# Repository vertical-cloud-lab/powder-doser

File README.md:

# Powder doser

**An open-source powder doser for autonomous alloy discovery, designed by engineers and modelled by AI agents.**

<p align="center">
  <a href="https://vertical-cloud-lab.github.io/powder-doser/"><b>Project page</b></a> ·
  <a href="https://github.com/vertical-cloud-lab/powder-doser/pull/209">Paper (in prep.)</a> ·
  <a href="https://vertical-cloud-lab.github.io/powder-doser/#build">CAD</a> ·
  <a href="https://www.youtube.com/watch?v=YmvaeqOQAU4&amp;t=514s">Talk</a> ·
  <a href="https://vertical-cloud-lab.github.io/powder-doser/#videos">Videos</a> ·
  <a href="https://vertical-cloud-lab.github.io/powder-doser/static/powder-doser-poster.pdf">Poster</a> ·
  <a href="https://vertical-cloud-lab.github.io/powder-doser/#talks">TMS 2027</a>
</p>

We built this doser at BYU's [Vertical Cloud Lab](https://github.com/vertical-cloud-lab) from 3D-printed parts and off-the-shelf electronics, for under $200 plus an analytical balance. One printed tube is both the powder reservoir and the dosing screw: the doser turns, tilts and taps it over a cup on the balance, which closes the loop, and an AI agent runs a dose when someone asks for one in a GitHub comment. Every 1 g dose on seven of the 13 powders we tested landed within ±5% of the target. **The [project page](https://vertical-cloud-lab.github.io/powder-doser/) has the rest:** the paper's figures, the CAD and firmware, the talk and videos, the poster and the TMS 2027 abstracts. The design discussion, the AI agents' work and the run data are in this repository's issues and pull requests.

<p align="center"></p>

<sub><b>Claude doses 8 g of Al 4047 for an atomizer charge</b> (30 Sep 2026, [#166](https://github.com/vertical-cloud-lab/powder-doser/pull/166)). Left, a phone's screen recording of the pull-request thread: Claude's checklist while the first pass runs, the follow-up to <code>@claude</code> typed on the phone after a clog, Claude's plan for a top-up, and its report. Right, the fixed camera over the balance at the same moment. 59 minutes in 22 s, sped up as marked. The full teaser on the [project page](https://vertical-cloud-lab.github.io/powder-doser/) starts with the auger being fitted.</sub>

<p align="center"></p>

<sub><b>A dose in three phases, replayed on the CAD</b> with the mass logged in the cup: bulk at 40° and 100 rpm with taps until 300 mg is left, trickle at 10° with no taps, then single taps at 15° until within 3 mg. The values in blue are the ones the optimizer sets, here the settings it recommended for 0.5 g of salt in the optimization campaign ([#166](https://github.com/vertical-cloud-lab/powder-doser/pull/166)), not those of the tests in the paper. Sped up as marked; from the campaign's slides ([#175](https://github.com/vertical-cloud-lab/powder-doser/pull/175)).</sub>

## Citation

Until the paper is out, please cite the repository:

```bibtex
@misc{charles2026powderdoser,
  title        = {An open-source powder doser for autonomous alloy discovery,
                  designed by engineers and modelled by AI agents},
  author       = {Charles, Sam and Mulberry, Will and Winters, Luke and
                  Robison, Carl and Erickson, Gage and Baird, Sterling G.},
  year         = {2026},
  note         = {Manuscript in preparation},
  howpublished = {\url{https://github.com/vertical-cloud-lab/powder-doser}}
}
```

## Outreach

A running list of individuals, academic groups, commercial vendors, and
open-source projects we could reach out to for help with accurate, automated
powder dispensing is kept in
[`paper/background/07-powder-dispensing-outreach-contacts.md`](paper/background/07-powder-dispensing-outreach-contacts.md)
(Edison-backed; per-entry `### Name` anchors and verifiable `(source: <URL>)`
tags). The synthesis is produced by
[`paper/background/edison_run_powder_dispensing_outreach_contacts.py`](paper/background/edison_run_powder_dispensing_outreach_contacts.py),
with raw artifacts under
[`paper/background/edison_artifacts/`](paper/background/edison_artifacts/),
and is compiled from the accelerated-discovery forum thread on [accurate
powder dispensing for chemistry and
materials-science applications](https://accelerated-discovery.org/t/accurate-powder-dispensing-for-chemistry-and-materials-science-applications/177),
the background notes in
[#29](https://github.com/vertical-cloud-lab/powder-doser/pull/29), and other
references throughout this repository. Same workflow as the generative-CAD
outreach note in [#43](https://github.com/vertical-cloud-lab/powder-doser/pull/43).

A companion list of **powder-properties** experts (flowability and
cohesion/friction measurement, DEM modeling and Bayesian calibration, AM
spreadability and powder-bed metrology) — anchored to the TMS 2027
calibration-optimization abstract from
[#78](https://github.com/vertical-cloud-lab/powder-doser/pull/78) — is kept
in
[`paper/background/08-powder-properties-experts.md`](paper/background/08-powder-properties-experts.md),
produced by
[`paper/background/edison_run_powder_properties_experts.py`](paper/background/edison_run_powder_properties_experts.py)
(three Edison `LITERATURE_HIGH` tasks plus direct web searching; raw
artifacts under the same
[`paper/background/edison_artifacts/`](paper/background/edison_artifacts/)
directory).

For actually reaching out, a narrowed **12-person shortlist** of the
powder-properties contacts who can *truly* help characterize powder for the
dynamic (DEM / cohesive-frictional) models — anchored to the on-device
characterization sweeps and tap / rapid-dose tests in
[#131](https://github.com/vertical-cloud-lab/powder-doser/pull/131), each with
a ready-to-send **template email** — is kept in
[`paper/background/09-powder-characterization-outreach-emails.md`](paper/background/09-powder-characterization-outreach-emails.md).

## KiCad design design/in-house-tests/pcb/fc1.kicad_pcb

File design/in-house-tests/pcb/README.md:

# FC-1: Faraday-cup charge amplifier board

**Status: design v1.0, 2026-11-28. Not built or tested.** KiCad 9.0.8 project for test 10 of
[`../SPEC.md`](../SPEC.md) (Faraday cup). ERC: 0 errors, 0 warnings. DRC: 0 errors, 0 unconnected pads,
schematic parity clean; 55 warnings, all the deliberate solder-mask opening over the guard (see
[Checks](#checks)).

| Top | Bottom (mirrored) |
|---|---|
|  |  |

Schematic: [`fc1-schematic.pdf`](fc1-schematic.pdf) ([SVG](fc1-schematic.svg), [PNG](fc1-schematic.png)).

## What it does

The inner cup of the Faraday cup is wired to the BNC. The board holds the cup at a virtual ground
and moves every coulomb that lands in the cup onto a feedback capacitor C_f. The output voltage is
proportional to the charge:

    Q_cup = -C_f * (V_OUT - V_REF)

An ADS1115 on the board reads V_OUT - V_REF differentially. It sits on the accessory Pico 2 W's
I2C chain (STEMMA QT, 3.3 V) at address 0x48. A reed relay across C_f zeroes the integrator when
the Pico drives GP10 high.

## The circuit in words

- **Input (guarded).** BNC J1 (Amphenol RF 031-5539, polypropylene insulator) centre pin to the
  inverting input of U1 (ADA4530-1, femtoampere electrometer op-amp, SOIC-8). This node, SUM, also
  goes to one side of C1, C2, R1 and the reed contact K1 pin 1, and nothing else. It is routed on the
  top layer only, with no vias. The only plated holes on it are the BNC centre pin and K1 pin 1.
- **Guard.** U1's guard-buffer pins (2 and 7) drive a GUARD copper fill around every SUM pad and
  trace, on both layers, 0.5 mm from SUM. The relay's coaxial shield (K1 pin 5) is on GUARD, so leakage
  from the coil lands on the guard, not on SUM. There is no solder mask over the guarded area (top and
  bottom), so surface leakage from other copper is caught by bare guard copper. A 2.2 mm hole (H6)
  next to U1 takes a Keystone 11301 PTFE turret if you want to air-wire the input instead.
- **Integrator.** C1 = 10 nF C0G 1 % is always in the feedback. Fitting the shunt on JP1 adds
  C2 = 100 nF C0G in parallel (C_f = 110 nF). R1 (1206, not fitted) is a place for a 10 G bleed
  resistor if slow drift ever matters more than holding a reading.
- **Reference.** U2 (REF3025, 2.500 V) sets U1's non-inverting input, the virtual ground, to mid-rail.
- **Reset.** K1 (Coto 9002-05-01: 1 Form A reed, 10^12 ohm minimum insulation, coaxial shield,
  internal coil diode) shorts C_f through R2 (100 R, limits the discharge current through the reed).
  GP10 high -> R11 4k7 -> Q1 (MMBT3904) pulls the 350 ohm, 5 V coil low (14 mA). D1 (1N4148W) is the
  flyback diode; R12 holds Q1 off if RESET_IN floats. D2 (yellow) lights while the relay is closed.
- **ADC.** U3 (ADS1115) runs at 5 V so it can see the whole 0-5 V output swing. AIN0 = OUT through
  R3 1k / C7 10 nF C0G, AIN1 = REF through the matching R4 / C8. AIN2, AIN3 and ALERT are unused.
  Address 0x48 through R10 (100k to GND); bridge one of JP2 / JP3 / JP4 for 0x49 / 0x4A / 0x4B.
- **I2C.** Q2, Q3 (BSS138) shift SDA and SCL between the 3.3 V bus (pull-ups R6, R7) and the ADC's
  5 V side (R8, R9). J2 and J3 are STEMMA QT / Qwiic sockets in parallel (pass-through).
- **Power.** 5 V from the Pico's VBUS on J4 pin 2. R5 (10 R) and C4 (10 uF) filter it into +5VA for
  U1, U2, U3. No LDO: U1's supply rejection and the differential read (REF noise cancels) make one
  unnecessary, and an LDO would leave too little headroom from 5 V (U1 needs at least 4.5 V). The
  relay coil and LEDs run on the unfiltered +5V. 3.3 V comes from the Pico (J4 pin 3 or the QT cable).
  D3 (green) shows 5 V.
- **Grounds.** One GND net poured on both layers and joined by 59 vias; no split planes (all
  currents are DC and under 20 mA). The outer can's M3 lug H5 joins GND only through R15 (0 R) near
  J4's GND pin: that is the single point where the shield meets circuit ground. Remove R15 to float the
  can, or replace it with an RC. JP5 sets the BNC shell: pads 1-2 bridged = shell on GND (default);
  2-3 = shell on GUARD (see [Leakage](#leakage-and-drift)).
- **Header J4** (2.54 mm): 1 GND, 2 5V, 3 3V3, 4 SDA, 5 SCL, 6 RESET_IN.

## Design numbers

### Range and resolution

U1's output swings to within about 0.1 V of the rails, so V_OUT - V_REF spans about +/-2.4 V.

| | C_f = 10 nF (JP1 open) | C_f = 110 nF (JP1 fitted) |
|---|---|---|
| Full scale | about +/-24 nC | about +/-264 nC |
| ADS1115 +/-4.096 V range (LSB 125 uV) | 1.25 pC per LSB | 13.8 pC per LSB |
| +/-2.048 V range (62.5 uV) | 0.63 pC | 6.9 pC |
| +/-0.256 V range (7.8 uV), for under 2.5 nC / 28 nC | 0.078 pC | 0.86 pC |

SPEC §10 expects 1-100 nC per gram, so a 0.1-1 g dose gives 0.1-100 nC: the 10 nF range for most
doses, 110 nF above about 20 nC. Auto-range in firmware by stepping the ADS1115's gain.

### Leakage and drift

A constant input current I moves the output by I * t / C_f.

| Source | Size | Drift on 10 nF | on 110 nF |
|---|---|---|---|
| U1 input bias (20 fA maximum: SPEC §10 and ADI's headline figure, not re-read here) | 20 fA | 1.2 pC/min = 0.12 mV/min | 0.011 mV/min |
| Reed contacts, open, 10^12 ohm minimum (10^13 typical) | proportional to the reading: 2.4 pA at full scale | at most 0.6 % of the reading per minute | same in % |
| Coil to contact | goes to the guarded shield, not to SUM | negligible | negligible |
| BNC and cable insulation, shell on GND (JP5 1-2) | 2.5 V across them; tens of fA when clean | about 0.1-1 pC/min | |
| FR-4 gap between the BNC centre and shell pins (0.94 mm, unguarded when JP5 is 1-2) | sub-pA clean and dry, can reach pA when humid or dirty | up to tens of pC/min | |

The last row is the weak point of a vertical BNC: its shell pin sits 2.54 mm from the centre pin, too
close for a guard trace. For charges under about 1 nC, or above about 50 % RH, bridge JP5 2-3 instead:
the shell (and the cable shield) then sit at the guard voltage, so there is no voltage across the BNC,
the cable or that gap. In that mode the cable shield must not touch the grounded outer can (use an
insulated feed-through at the can, ground the can with the lug H5), and the BNC must not touch a
grounded metal panel. The leakage figures for the gap are estimates, not measurements: measure the
drift with the drift test below and log RH with the SHT45.

The relay term acts like a 10^12 ohm resistor across C_f (time constant 10^4 s on 10 nF), so a reading
taken within a minute of the reset loses at most about 0.6 % and usually much less.

### Reset

- K1 closes in about 0.35 ms (Coto data sheet, typical, including bounce).
- C_f discharges through R2: time constant 1 us (10 nF) or 11 us (110 nF); U1 then holds OUT = REF.
- Recommended: GP10 high for 100 ms (1 s after a near-full-scale reading), then low, wait 50 ms, take
  the baseline reading.
- Opening the relay injects a small fixed charge (the coil swings 5 V; coil-to-contact capacitance
  is 0.5 pF with the shield guarded, so at most about 2.5 pC). The baseline taken after release
  removes it.

### Dielectric absorption

After a reset, a capacitor gives back a small fraction of its previous voltage over seconds to
minutes. C0G ceramic is among the best dielectrics for this (typically 0.1 % or less), with
polypropylene or polystyrene film better still. After a full-scale 2.4 V reading, expect at most a
few mV (tens of pC on 10 nF) to creep back. Hold the reset for 1 s after large readings and always
read a fresh baseline after the reset. If it matters, replace C1 with a 10 nF polypropylene film
capacitor on short leads (WIMA FKP2) on the same pads.

### Input capacitance and noise gain

C_in = cup to can (10-30 pF) + cable (RG-58 is about 100 pF/m: about 30 pF for 0.3 m) + BNC, PCB and
U1 (a few pF): about 50-70 pF. The charge amplifier collects the charge regardless of C_in (the cup
stays at the virtual ground), but C_in sets the noise gain 1 + C_in / C_f = 1.006 on 10 nF and
1.0006 on 110 nF. So U1's voltage noise reaches the output almost unamplified: a few uV, far below
the ADC's LSB. Because the cup sits at +2.5 V relative to the grounded can, a change in their
capacitance moves charge: 0.1 pF of vibration or powder gives 0.25 pC. That sets a floor for the
smallest charges, not for nC readings.

## Board

- 50 x 40 mm, 2 layers, 1.6 mm FR-4, 1 oz. Four M3 holes (NPTH) 3.5 mm from each corner
  (43 x 33 mm pattern), M3 plated lug H5 for the outer can, 2.2 mm hole H6 for the PTFE turret.
- Hand-solderable: 0805 and 1206 passives, SOT-23, SOD-123, SOIC-8, MSOP-10 (0.5 mm pitch, the
  hardest part), JST SH sockets, through-hole headers, relay and BNC.
- Design rules (JLCPCB- and OSH Park-safe): 0.15 mm minimum track and clearance, 0.6 / 0.3 mm vias,
  0.3 mm copper to edge. Default clearance 0.2 mm, SUM 0.5 mm. `fc1.kicad_dru` allows the MSOP-10's
  own 0.15 mm pad gaps.
- Silkscreen: name, version, date, J4 pin names, LED and range labels, address codes, JP5 pads, CAN.
  `JLCJLCJLCJLC` on the back marks where JLCPCB may print its order number (keep it off the guard).

## Ordering

| Fab | Price | Build + shipping to Utah | Source |
|---|---|---|---|
| JLCPCB | from $2 for 5 boards (2 layers, up to 100 x 100 mm, green, HASL); ENIG extra | 24 h build (green); DHL Express 3-5 business days, Global Standard Direct Line 8-10 | jlcpcb.com home page offer; shipping table at jlcpcb.com/help/article/Shipping-Methods-and-Delivery-Time (updated 2026-11-10) |
| OSH Park | $5 per square inch for 3: 3.10 in^2 = **$15.50 for 3** (ENIG, purple, 1.6 mm) | ships in 9-12 calendar days, free USPS First Class 1-5 business days; Super Swift $31.00, ships within 5 business days | docs.oshpark.com (services/two-layer, super-swift, shipping-information) |

Not verified: the exact JLCPCB quote for this board and the shipping cost (both need the quote page
in a browser). Expect about 1 week door to door from JLCPCB with DHL, about 2-2.5 weeks from OSH Park.

- **JLCPCB:** upload `fc1-gerbers.zip`; 2 layers, 1.6 mm, 50 x 40 mm, qty 5. Pick **ENIG** if you
  can (the guard area is bare copper; HASL works but is lumpier). Order number: "Specify a location".
  Do not let anyone "fix" the mask opening over the input: it is on purpose.
- **OSH Park:** upload `fc1-gerbers.zip` (or `fc1.kicad_pcb`). ENIG is standard.
- **Parts:** [`bom.csv`](bom.csv): 29 part lines (40 parts fitted, R1 not fitted) plus the optional PTFE turret and the PCB, with DigiKey part numbers, prices and stock read from
  DigiKey's own product pages on 2026-11-28. About **$72 per board** at single-unit prices, about
  $58 at 10-off prices, plus the PCB. The ADA4530-1 alone is $41.95 (103 in stock, 44-week factory
  lead time: buy it first). Out-of-stock first choices were swapped for in-stock equivalents (listed
  as alternates). The JST, header and Ohmite alternates were not checked.

## Assembly

[`solder_steps.json`](solder_steps.json) lists the 41 steps in order (also the source for the
soldering animation): ICs first (U3, U1), then SOT-23 and SOD-123 parts, the 0805 resistors and
capacitors, LEDs, the 1206 parts, the JP5 bridge, the JST sockets, the headers, the relay and
finally the BNC. Positions are in mm from the board's lower-left corner, y up.

- Use rosin or water-washable flux, not no-clean, and wash the whole board in 99 % IPA with a soft
  brush. Rinse the guard area last with fresh IPA, then dry it (warm air or 1 h at 50 C).
- Hold the board by its edges after washing; skin oil on the guard area is a leakage path.
- Bridge JP5 pads 1-2 (shell on GND) for the first tests. Leave JP2-JP4 open (address 0x48).
- R1 is not fitted. Fit the JP1 shunt only for the 110 nF range.

## Bench test

1. **Power.** Wire J4 to the Pico: GND, 5V to VBUS (pin 40), 3V3 to 3V3(OUT) (pin 36), SDA to GP0,
   SCL to GP1, RST to GP10. Always connect J4's 5 V: with 3.3 V but no 5 V, the BSS138 body diodes
   load the I2C bus and the other sensors on the chain stop answering. Check: D3 on; REF at C6 =
   2.500 V +/- 5 mV; the bare guard copper reads the same about 2.50 V on a DMM (never probe SUM);
   an I2C scan shows 0x48; D2 lights while GP10 is high.
2. **Drift (leakage).** Cap the BNC, reset, log OUT - REF at 8 SPS on the +/-0.256 V range for 10 min.
   Leakage I = C_f * slope. Clean and dry, expect under 0.12 mV/min on 10 nF (20 fA). Log RH and T.
3. **Known charge.** Put a 1.00 nF +/-1 % C0G capacitor in series with the BNC centre (a BNC tee or a
   short BNC-to-clip lead), its other end on a source that steps from 0 to 1.000 V, with the source's
   ground on the board's GND. Q = C_inj * dV = 1.00 nC, so V_OUT - V_REF should step by
   **-100.0 mV** on 10 nF and **-9.09 mV** on 110 nF. Stepping back to 0 V should return it to the
   baseline. Other useful points: 10.0 nF injection -> -1.000 V on 10 nF (gain -1: checks C1 against
   C_inj); 10 pF -> 10 pC -> -1.00 mV (use the +/-0.256 V range). The Pico can be the source: a GPIO
   step is 3.3 V, so 1 nF injects 3.3 nC (measure the GPIO's high level with a DMM first).
4. **Reset.** Inject 10 nC, pulse GP10 for 100 ms: the reading should come back to the baseline
   within a few LSB. Log the next 60 s to see the dielectric-absorption creep.
5. **Range.** Fit JP1 and repeat step 3 with a 10.0 nF injection: expect -90.9 mV.

## Reading it from the accessory Pico

I2C0 on GP0 (SDA) / GP1 (SCL), address 0x48. ADS1115 config register (0x01) for a single-shot
AIN0 - AIN1 conversion at 8 SPS, comparator off: `0x8303` (+/-4.096 V, the full swing), `0x8503`
(+/-2.048 V), `0x8B03` (+/-0.256 V). Use 8 SPS for single readings (lowest noise) and 128-860 SPS
for time series. Reset is GP10 (SPEC §0.2): high = relay closed.

```python
# MicroPython, accessory Pico 2 W
from machine import I2C, Pin
import struct, time

i2c = I2C(0, sda=Pin(0), scl=Pin(1), freq=100_000)
rst = Pin(10, Pin.OUT, value=0)
ADDR, C_F = 0x48, 10e-9            # 110e-9 with the JP1 shunt fitted
PGA = {4.096: 1, 2.048: 2, 1.024: 3, 0.512: 4, 0.256: 5}

def volts(fsr=4.096):
    """One AIN0-AIN1 reading at 8 SPS, in volts (V_OUT - V_REF)."""
    cfg = 0x8000 | (PGA[fsr] << 9) | 0x0100 | 0x0003   # OS, AIN0-AIN1, gain, single-shot, 8 SPS, comp off
    i2c.writeto_mem(ADDR, 0x01, struct.pack(">H", cfg))
    while not i2c.readfrom_mem(ADDR, 0x01, 2)[0] & 0x80:
        time.sleep_ms(5)
    return struct.unpack(">h", i2c.readfrom_mem(ADDR, 0x00, 2))[0] * fsr / 32768

def zero(hold_ms=100):
    rst.on(); time.sleep_ms(hold_ms); rst.off(); time.sleep_ms(50)
    return volts()

v0 = zero()
# ... dose N revs, wait 2 s after the last grain (SPEC §10) ...
q = -C_F * (volts() - v0)          # coulombs collected by the inner cup
```

## Files

| File | What |
|---|---|
| `fc1.kicad_pro`, `fc1.kicad_sch`, `fc1.kicad_pcb`, `fc1.kicad_dru` | KiCad 9 project |
| `fc1.kicad_sym`, `fc1.pretty/`, `sym-lib-table`, `fp-lib-table` | project library: the Coto 9002 symbol and SIP-6 footprint (drawn from the Coto data sheet; everything else is from KiCad's own libraries) |
| `fc1_design.py` | single source: parts, nets, MPNs, placement, guard polygon, silkscreen |
| `gen_sch.py`, `gen_pro.py`, `build_pcb.py`, `sexp.py` | generators for the schematic, project file and board |
| `fc1.dsn`, `fc1.ses` | autorouter input and result (FreeRouting 2.6.0) |
| `make_bom.py`, `bom.csv` | BOM with DigiKey data |
| `make_solder_steps.py`, `solder_steps.json` | soldering order and geometry for the animation |
| `export.sh` | ERC, DRC, schematic PDF/SVG, Gerbers, drill, position file and renders |
| `fc1-schematic.pdf/.svg/.png`, `fc1-top.png`, `fc1-bottom.png`, `fc1-iso.png` | outputs |
| `gerbers/`, `fc1-gerbers.zip`, `fc1-pos.csv` | fabrication outputs (position file origin = board lower-left, y up) |
| `erc.rpt`, `drc.rpt` | check reports |

To regenerate (KiCad 9 `pcbnew` needs the system Python):

```bash
python3 gen_pro.py && python3 gen_sch.py
/usr/bin/python3 build_pcb.py place          # footprints, nets, the hand-routed guarded input
/usr/bin/python3 build_pcb.py dsn            # fc1.dsn with the guard area kept out
java -jar freerouting-2.6.0.jar -de fc1.dsn -do fc1.ses -mp 40 -mt 1 --gui.enabled=false   # Java 25
/usr/bin/python3 build_pcb.py finish         # import routes, guard and GND pours, mask opening, silk
./export.sh && python3 make_bom.py && /usr/bin/python3 make_solder_steps.py
```

The hand-routed parts are the SUM traces, the guard link between U1 pins 7 and 2, U1's feedback
connections and the BNC shell link; FreeRouting routed the rest (some traces neck to 0.15 mm at the
MSOP-10 pins). The renders used the 12 KiCad 3D models this board needs, fetched from
gitlab.com/kicad/libraries/kicad-packages3D (tag 9.0.8); KiCad has no model for the BNC and the relay
footprint is the project's own, so those two show as bare pads.

## Checks

- **ERC** ([`erc.rpt`](erc.rpt)): 0 errors, 0 warnings. A netlist export was also compared pin by pin
  with `fc1_design.py`: no differences.
- **DRC** ([`drc.rpt`](drc.rpt), with schematic parity): 0 errors, 0 unconnected pads, 0 footprint or
  parity problems. 55 warnings, all `solder_mask_bridge`: the mask opening over the guarded area
  exposes SUM and GUARD copper (and 14 GUARD vias) in one aperture. That is the intended guard layout,
  not a fault.

## Not verified / open points

- **ADA4530-1 pinout** is from KiCad's library symbol (1 +IN, 2 and 7 guard, 3 "IC", 4 V-, 5 V+,
  6 OUT, 8 -IN); analog.com timed out from the runner, so the data sheet was not re-read. Pin 3 is
  left unconnected. Check pin 3 and the guard-buffer load limits against the data sheet before ordering.
- **Coto 9002 footprint** was drawn from the data sheet (6 pins on a 2.54 mm grid: 1, 5, 2, gap, 3,
  6, 4; body 19.3 x 5.08 mm, 5.6 mm with shell). Check it against a real relay or a 1:1 print.
- **BNC.** The first choice, TE 1-1478035-0 (right angle, PTFE), is obsolete, and no in-stock
  right-angle PTFE BNC could be matched to a verified footprint, so the board uses the vertical
  bulkhead Amphenol 031-5539 with KiCad's footprint for that part. Mount the board behind a panel with
  the BNC through it.
- Fab prices and shipping (above); the leakage of the BNC pin gap (estimate only); the body heights
  in `solder_steps.json` are approximate package outlines.
- The board has not been built. Build one, run the bench test, then update this file.

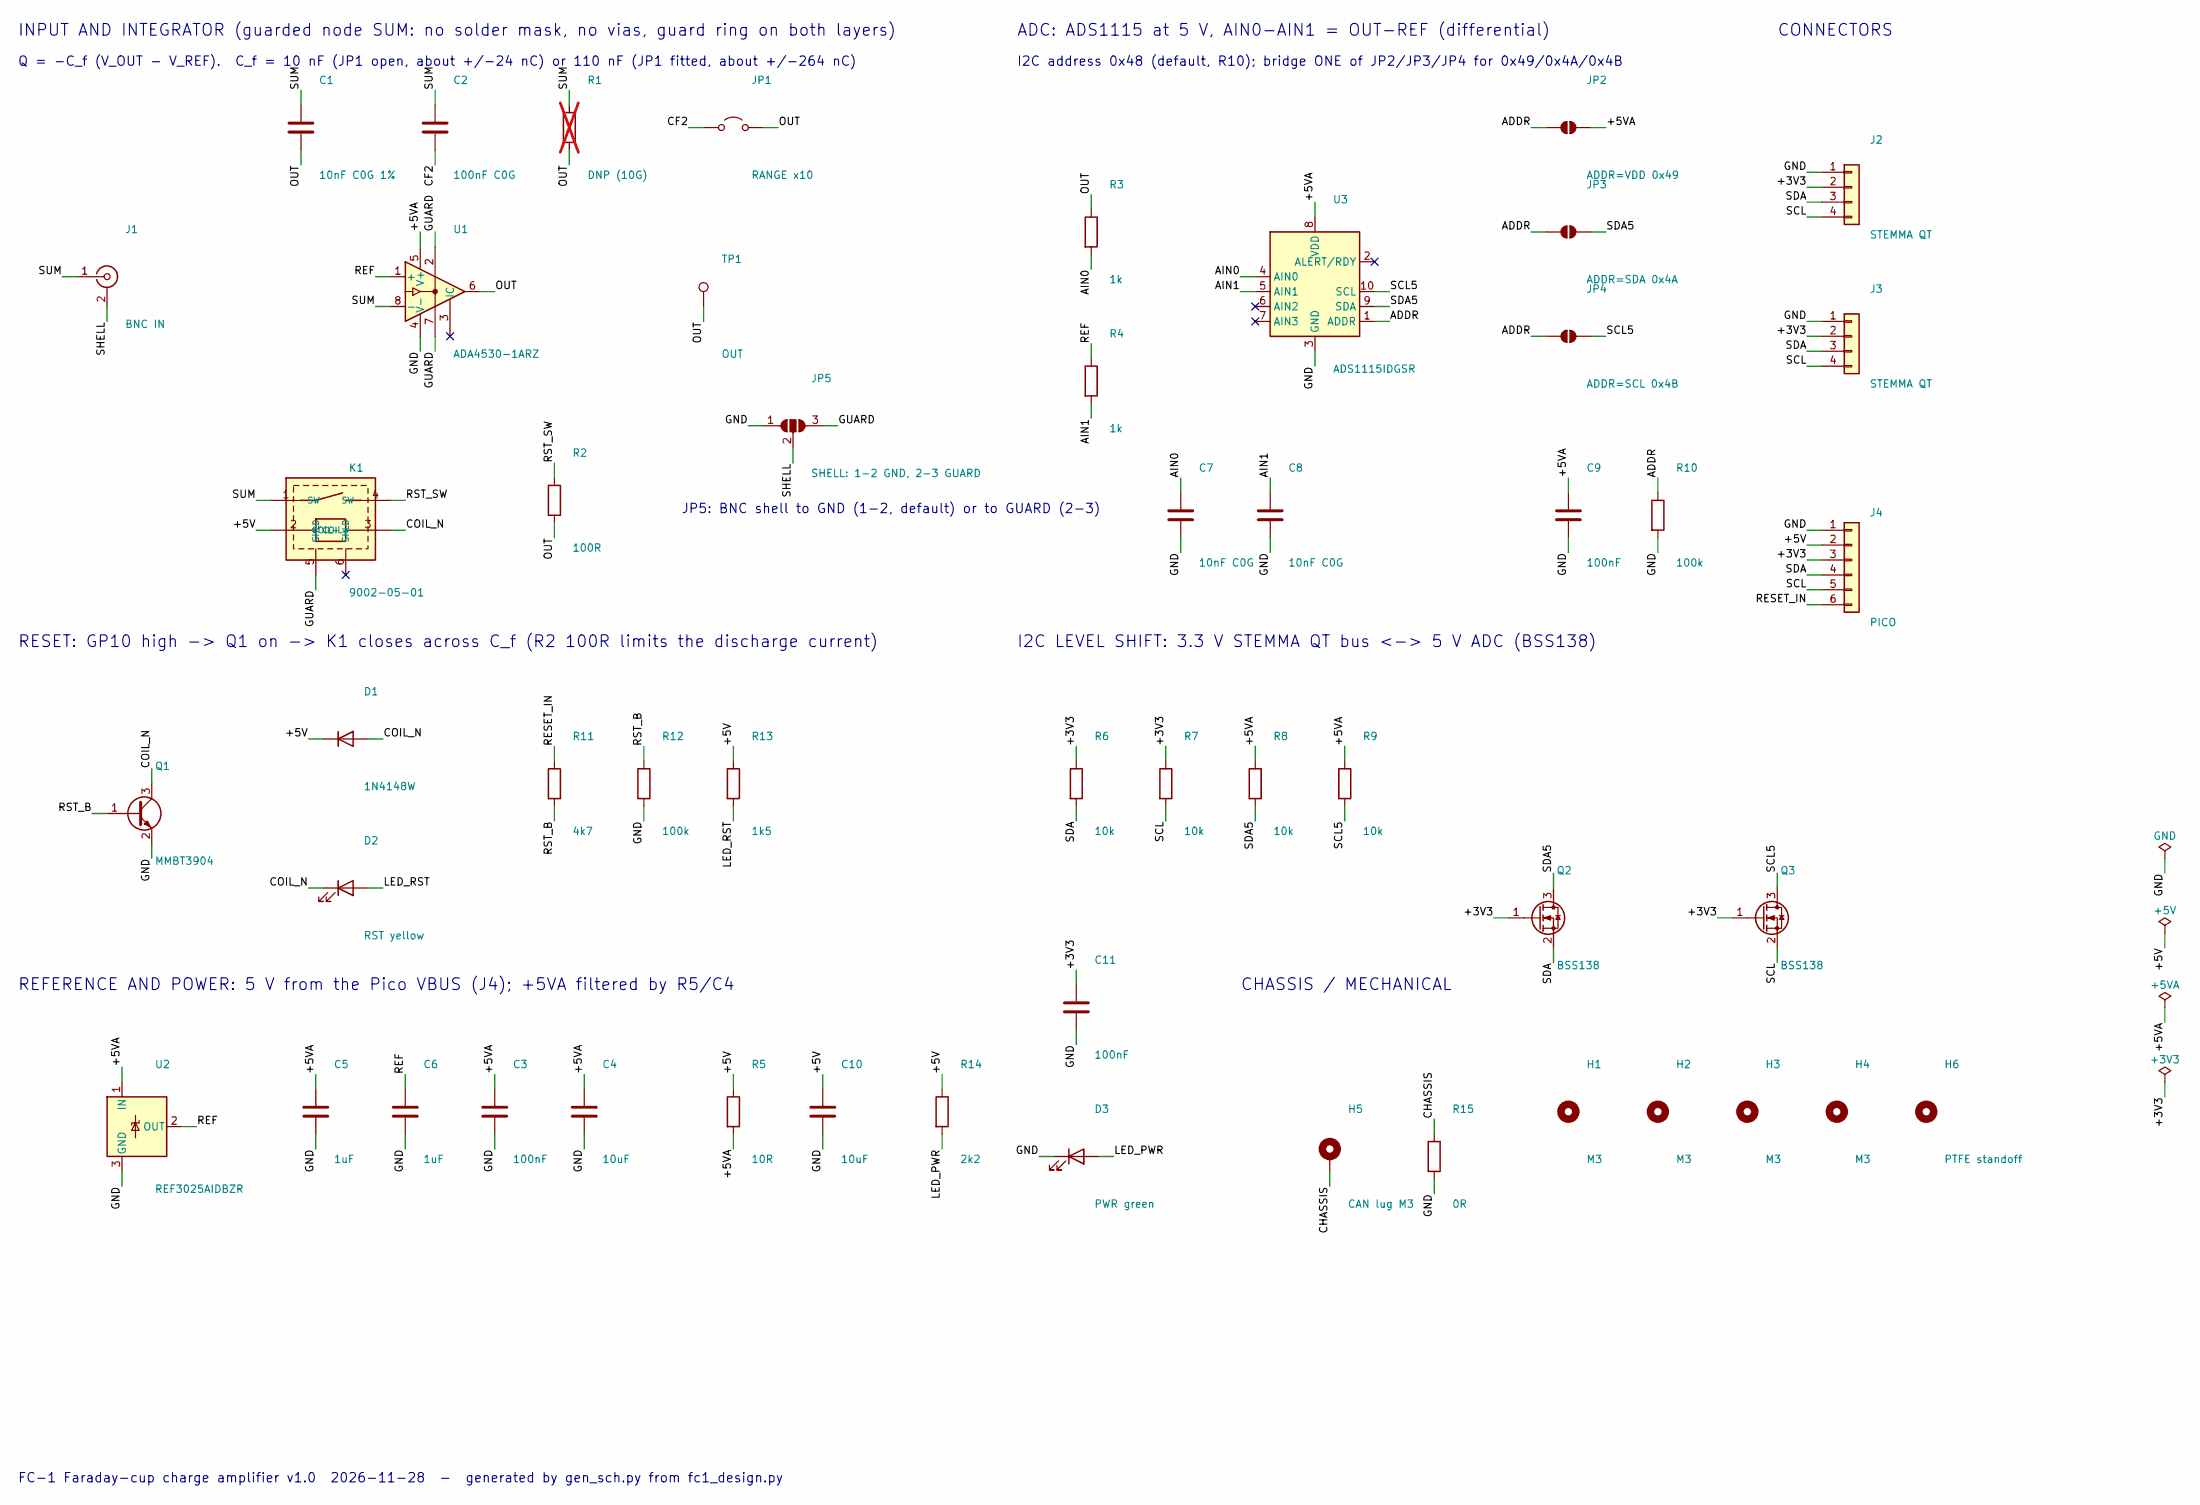
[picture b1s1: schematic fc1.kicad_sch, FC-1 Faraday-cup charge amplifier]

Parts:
C1: 10nF C0G 1%; C_1206_3216Metric_Pad1.33x1.80mm_HandSolder; MPN CC1206FKNPO9BN103
C2: 100nF C0G; C_1206_3216Metric_Pad1.33x1.80mm_HandSolder; MPN C3216C0G1H104J160AA
C3, C9, C11: 100nF; C_0805_2012Metric_Pad1.18x1.45mm_HandSolder; MPN CL21B104KBCNNNC
C4, C10: 10uF; C_0805_2012Metric_Pad1.18x1.45mm_HandSolder; MPN GRM21BR61E106KA73L
C5, C6: 1uF; C_0805_2012Metric_Pad1.18x1.45mm_HandSolder; MPN CL21B105KAFNNNE
C7, C8: 10nF C0G; C_0805_2012Metric_Pad1.18x1.45mm_HandSolder; MPN GRM2195C1H103JA01D
D1: 1N4148W; D_SOD-123; MPN 1N4148W-TP
D2: RST yellow; LED_0805_2012Metric_Pad1.15x1.40mm_HandSolder; MPN LTST-C171KSKT
D3: PWR green; LED_0805_2012Metric_Pad1.15x1.40mm_HandSolder; MPN LTST-C171GKT
H1, H2, H3, H4: M3; MountingHole_3.2mm_M3
H5: CAN lug M3; MountingHole_3.2mm_M3_Pad_Via
H6: PTFE standoff; MountingHole_2.2mm_M2
J1: BNC IN; BNC_Amphenol_031-5539_Vertical; MPN 031-5539
J2, J3: STEMMA QT; JST_SH_SM04B-SRSS-TB_1x04-1MP_P1.00mm_Horizontal; MPN SM04B-SRSS-TB(LF)(SN)
J4: PICO; PinHeader_1x06_P2.54mm_Vertical; MPN PREC006SAAN-RC
JP1: RANGE x10; PinHeader_1x02_P2.54mm_Vertical; MPN PREC002SAAN-RC + SPC02SYAN
JP2: ADDR=VDD 0x49; SolderJumper-2_P1.3mm_Open_RoundedPad1.0x1.5mm
JP3: ADDR=SDA 0x4A; SolderJumper-2_P1.3mm_Open_RoundedPad1.0x1.5mm
JP4: ADDR=SCL 0x4B; SolderJumper-2_P1.3mm_Open_RoundedPad1.0x1.5mm
JP5: SHELL: 1-2 GND, 2-3 GUARD; SolderJumper-3_P1.3mm_Open_RoundedPad1.0x1.5mm_NumberLabels
K1: 9002-05-01; Relay_SPST-NO_Coto_9002_SIP6; MPN 9002-05-01
Q1: MMBT3904; SOT-23; MPN MMBT3904LT1G
Q2, Q3: BSS138; SOT-23; MPN BSS138
R1: DNP (10G); R_1206_3216Metric_Pad1.30x1.75mm_HandSolder; MPN HVC1206Z1008KET; not fitted
R2: 100R; R_0805_2012Metric_Pad1.20x1.40mm_HandSolder; MPN RMCF0805FT100R
R3, R4: 1k; R_0805_2012Metric_Pad1.20x1.40mm_HandSolder; MPN RC0805FR-071KL
R5: 10R; R_0805_2012Metric_Pad1.20x1.40mm_HandSolder; MPN RC0805FR-0710RL
R6, R7, R8, R9: 10k; R_0805_2012Metric_Pad1.20x1.40mm_HandSolder; MPN RC0805FR-0710KL
R10, R12: 100k; R_0805_2012Metric_Pad1.20x1.40mm_HandSolder; MPN RC0805FR-07100KL
R11: 4k7; R_0805_2012Metric_Pad1.20x1.40mm_HandSolder; MPN RC0805FR-074K7L
R13: 1k5; R_0805_2012Metric_Pad1.20x1.40mm_HandSolder; MPN RC0805FR-071K5L
R14: 2k2; R_0805_2012Metric_Pad1.20x1.40mm_HandSolder; MPN RC0805FR-072K2L
R15: 0R; R_1206_3216Metric_Pad1.30x1.75mm_HandSolder; MPN RC1206JR-070RL
TP1: OUT; TestPoint_THTPad_D1.5mm_Drill0.7mm
U1: ADA4530-1ARZ; SOIC-8_3.9x4.9mm_P1.27mm; MPN ADA4530-1ARZ
U2: REF3025AIDBZR; SOT-23; MPN REF3025AIDBZR
U3: ADS1115IDGSR; MSOP-10_3x3mm_P0.5mm; MPN ADS1115IDGSR

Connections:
/+3V3: C11.1, J2.2, J3.2, J4.3, Q2.1 (G), Q3.1 (G), R6.1, R7.1
/+5V: C10.1, D1.1 (K), J4.2, K1.2 (COIL+), R5.1, R13.1, R14.1
/+5VA: C3.1, C4.1, C5.1, C9.1, JP2.2 (B), R5.2, R8.1, R9.1, U1.5 (V+), U2.1 (IN), U3.8 (VDD)
/ADDR: JP2.1 (A), JP3.1 (A), JP4.1 (A), R10.1, U3.1 (ADDR)
/AIN0: C7.1, R3.2, U3.4 (AIN0)
/AIN1: C8.1, R4.2, U3.5 (AIN1)
/CF2: C2.2, JP1.1 (A)
/CHASSIS: H5.1, R15.1
/COIL_N: D1.2 (A), D2.1 (K), K1.3 (COIL-), Q1.3 (C)
/GND: C3.2, C4.2, C5.2, C6.2, C7.2, C8.2, C9.2, C10.2, C11.2, D3.1 (K), J2.1, J3.1, J4.1, JP5.1 (A), Q1.2 (E), R10.2, R12.2, R15.2, U1.4 (V-), U2.3 (GND), U3.3 (GND)
/GUARD: JP5.3 (B), K1.5 (SHLD), U1.2, U1.7
/LED_PWR: D3.2 (A), R14.2
/LED_RST: D2.2 (A), R13.2
/OUT: C1.2, JP1.2 (B), R1.2, R2.2, R3.1, TP1.1, U1.6
/REF: C6.1, R4.1, U1.1 (+), U2.2 (OUT)
/RESET_IN: J4.6, R11.1
/RST_B: Q1.1 (B), R11.2, R12.1
/RST_SW: K1.4 (SW), R2.1
/SCL: J2.4, J3.4, J4.5, Q3.2 (S), R7.2
/SCL5: JP4.2 (B), Q3.3 (D), R9.2, U3.10 (SCL)
/SDA: J2.3, J3.3, J4.4, Q2.2 (S), R6.2
/SDA5: JP3.2 (B), Q2.3 (D), R8.2, U3.9 (SDA)
/SHELL: J1.2 (Ext), JP5.2 (C)
/SUM: C1.1, C2.1, J1.1 (In), K1.1 (SW), R1.1, U1.8 (-)

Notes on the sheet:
INPUT AND INTEGRATOR (guarded node SUM: no solder mask, no vias, guard ring on both layers)
Q = -C_f (V_OUT - V_REF). C_f = 10 nF (JP1 open, about +/-24 nC) or 110 nF (JP1 fitted, about +/-264 nC)
RESET: GP10 high -> Q1 on -> K1 closes across C_f (R2 100R limits the discharge current)
REFERENCE AND POWER: 5 V from the Pico VBUS (J4); +5VA filtered by R5/C4
ADC: ADS1115 at 5 V, AIN0-AIN1 = OUT-REF (differential)
I2C address 0x48 (default, R10); bridge ONE of JP2/JP3/JP4 for 0x49/0x4A/0x4B
I2C LEVEL SHIFT: 3.3 V STEMMA QT bus <-> 5 V ADC (BSS138)
CONNECTORS
CHASSIS / MECHANICAL
JP5: BNC shell to GND (1-2, default) or to GUARD (2-3)
FC-1 Faraday-cup charge amplifier v1.0 2026-11-28 - generated by gen_sch.py from fc1_design.py

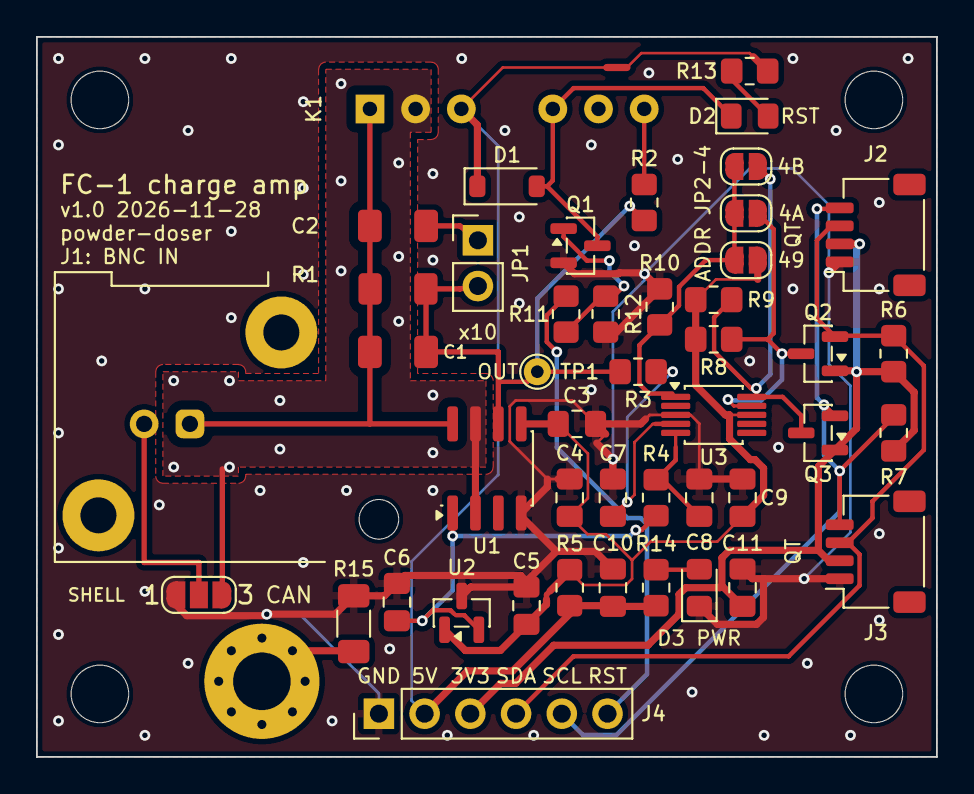
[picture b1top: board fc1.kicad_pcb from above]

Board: 2 copper layers, 50.0 x 40.0 mm, 52 parts (0 on the bottom side), 24 nets.

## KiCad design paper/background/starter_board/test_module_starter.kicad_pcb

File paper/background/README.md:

# Background research for the BYU NASA Space Grant proposal

This folder collects literature and landscape reviews to inform the
**background section** of the grant proposal scaffolded under
[`paper/main.tex`](../main.tex) (see issue
[#26](https://github.com/vertical-cloud-lab/powder-doser/issues/26)).

The proposal is framed around generative CAD applied to this repository
(`powder-doser`), tied to a larger vision of autonomous discovery of
additively manufactured (AM) aerospace alloys, where accurate multi-powder
dosing is a critical unmet need. Two background pillars therefore need to be
covered, each addressed by both a *landscape* review (commercial / tool-level
state of the art) and a *literature* review (recent peer-reviewed work):

| File | Pillar | Scope |
| --- | --- | --- |
| [`01-powder-dispensing-commercial-landscape.md`](01-powder-dispensing-commercial-landscape.md) | Powder dispensing | Commercial systems (Mettler Toledo Quantos/CHRONECT, Chemspeed SWING/FLEX, Unchained Labs, Coperion K-Tron, Schenck, Gericke, Brabender, Movacolor, Freeman FT4, Sartorius), accuracy/throughput/price, gap analysis for sub-$10k AM-capable multi-powder dosing. References issue [#10](https://github.com/vertical-cloud-lab/powder-doser/issues/10). |
| [`02-powder-dispensing-academic-literature.md`](02-powder-dispensing-academic-literature.md) | Powder dispensing | Recent (2018–2025) peer-reviewed papers on automated dosing, multi-material/HT metal AM (Ni, Ti, HEAs, refractory alloys), compositionally graded alloy discovery, self-driving labs handling solids, and powder-flowability characterization. |
| [`03-generative-cad-landscape.md`](03-generative-cad-landscape.md) | Generative CAD | Commercial (Fusion Generative Design, nTop, Siemens NX, PTC Creo, ANSYS Discovery, Altair Inspire, Rhino + Grasshopper) and code-based / parametric (CadQuery, OpenSCAD, build123d, Onshape FeatureScript, JSCAD) tools, plus AI/LLM-driven CAD research, with capability and limitation comparisons. References issue [#6](https://github.com/vertical-cloud-lab/powder-doser/issues/6). |
| [`04-generative-cad-academic-literature.md`](04-generative-cad-academic-literature.md) | Generative CAD | Recent (2021–2025) peer-reviewed and arXiv work on generative CAD, AI-assisted CAD, LLM-based CAD code generation, programmatic CAD, and learning-based shape generation, plus landmark datasets (DeepCAD, Fusion 360 Gallery, ABC, SketchGraphs, Text2CAD). |
| [`05-llm-cad-spatial-reasoning-mitigation.md`](05-llm-cad-spatial-reasoning-mitigation.md) | Generative CAD | Synthesis (triggered by [PR #34 comment 4433787200](https://github.com/vertical-cloud-lab/powder-doser/pull/34#issuecomment-4433787200)) on LLM/agent spatial-reasoning + assembly failures observed in [PR #35](https://github.com/vertical-cloud-lab/powder-doser/pull/35) (Claude Opus 4.7 CadQuery), with concrete tool-side / prompting / representation / human-in-the-loop mitigations. Backed by a follow-up Edison `LITERATURE_HIGH` query (see below). |
| [`06-tools-and-repositories-to-try.md`](06-tools-and-repositories-to-try.md) | Both | Synthesis (triggered by [PR #29 comment 4434939162](https://github.com/vertical-cloud-lab/powder-doser/pull/29#issuecomment-4434939162)) re-organising the tools cited across `01`–`05` around what can actually be cloned, installed, or subscribed to today: code-CAD foundations (CadQuery, build123d, OCP, FreeCAD, slicers), 2024–2026 LLM-CAD research repos (CADSmith, CAD-Coder, CAD-Recode, Text-to-CadQuery, CAD-MLLM, CADCrafter, …), datasets, commercial subscriptions worth trialling (Onshape, Zoo.dev) vs. ones to skip on the proposal budget (nTop, Creo, NX), and a 6-step recommended trial set. Connects to [PR #7](https://github.com/vertical-cloud-lab/powder-doser/pull/7)'s open-source CAD tooling work. |

## Provenance

These notes were produced by four parallel
[Edison Scientific](https://edisonscientific.gitbook.io/edison-cookbook)
`LITERATURE_HIGH` queries (the `paperqa`-class deep literature pipeline). Each
claim in the notes is followed by a citation key of the form
`(authorYYYYshortid pages X-Y)`; the corresponding numbered references — with
authors, journal, DOI, and citation count — are listed at the bottom of each
file.

The notes are intentionally kept verbatim (lightly formatted markdown) rather
than paraphrased, so that citation provenance to the underlying sources is
preserved when individual passages are pulled into the LaTeX manuscript.

## How to use these notes when drafting the proposal

1. Skim each file's table of contents (`##` section headings) and the
   *Conclusions / Key takeaways* sections at the end.
2. Pull specific claims into the proposal's Background and Motivation
   sections, replacing the inline `(authorYYYY... pages ...)` Edison citation
   keys with `\cite{...}` calls into [`paper/rsc.bib`](../rsc.bib).
3. For any reference cited in the proposal, copy the corresponding entry from
   the file's *References* section into `paper/rsc.bib` as a proper BibTeX
   entry (the DOI is provided in every Edison reference). Only references
   that are actually cited in the manuscript should end up in `rsc.bib` —
   leave the broader bibliography here in the notes for traceability.
4. The *Technology Gap Analysis* table in
   `01-powder-dispensing-commercial-landscape.md` and the
   *Capabilities vs. Limitations* discussion in
   `03-generative-cad-landscape.md` and
   `04-generative-cad-academic-literature.md` are particularly relevant
   for motivating the proposal's research questions.

## Raw query artifacts (provenance)

The full raw outputs from Edison — including the underlying contexts,
references, agent state, cost, and token counts — are committed under
[`edison_artifacts/`](edison_artifacts/) for reproducibility. Each query has
three files (`<key>.task.json`, `<key>.answer.md`, `<key>.references.md`); see
[`edison_artifacts/README.md`](edison_artifacts/README.md) for layout.

## Reproducing or refreshing the notes

The four original queries can be re-run end-to-end with
[`edison_run.py`](edison_run.py); the follow-up spatial-reasoning query that
backs `05-llm-cad-spatial-reasoning-mitigation.md` lives in
[`edison_run_followup_spatial.py`](edison_run_followup_spatial.py). Both
embed their prompts verbatim and write the artifacts described above:

Both runners read the API key from the `EDISON_API_KEY` environment variable
via `os.environ["EDISON_API_KEY"]` (never hard-coded or logged):

```sh
pip install edison_client
export EDISON_API_KEY=...   # never commit this value
python paper/background/edison_run.py
python paper/background/edison_run_followup_spatial.py
```

A high-effort literature query takes roughly 20–30 minutes per task; all four
are dispatched in parallel via `EdisonClient.run_tasks_until_done`.

The prompts are also quoted verbatim at the top of each `0*-*.md` file (the
`Question:` line), so they can be edited and re-run independently.

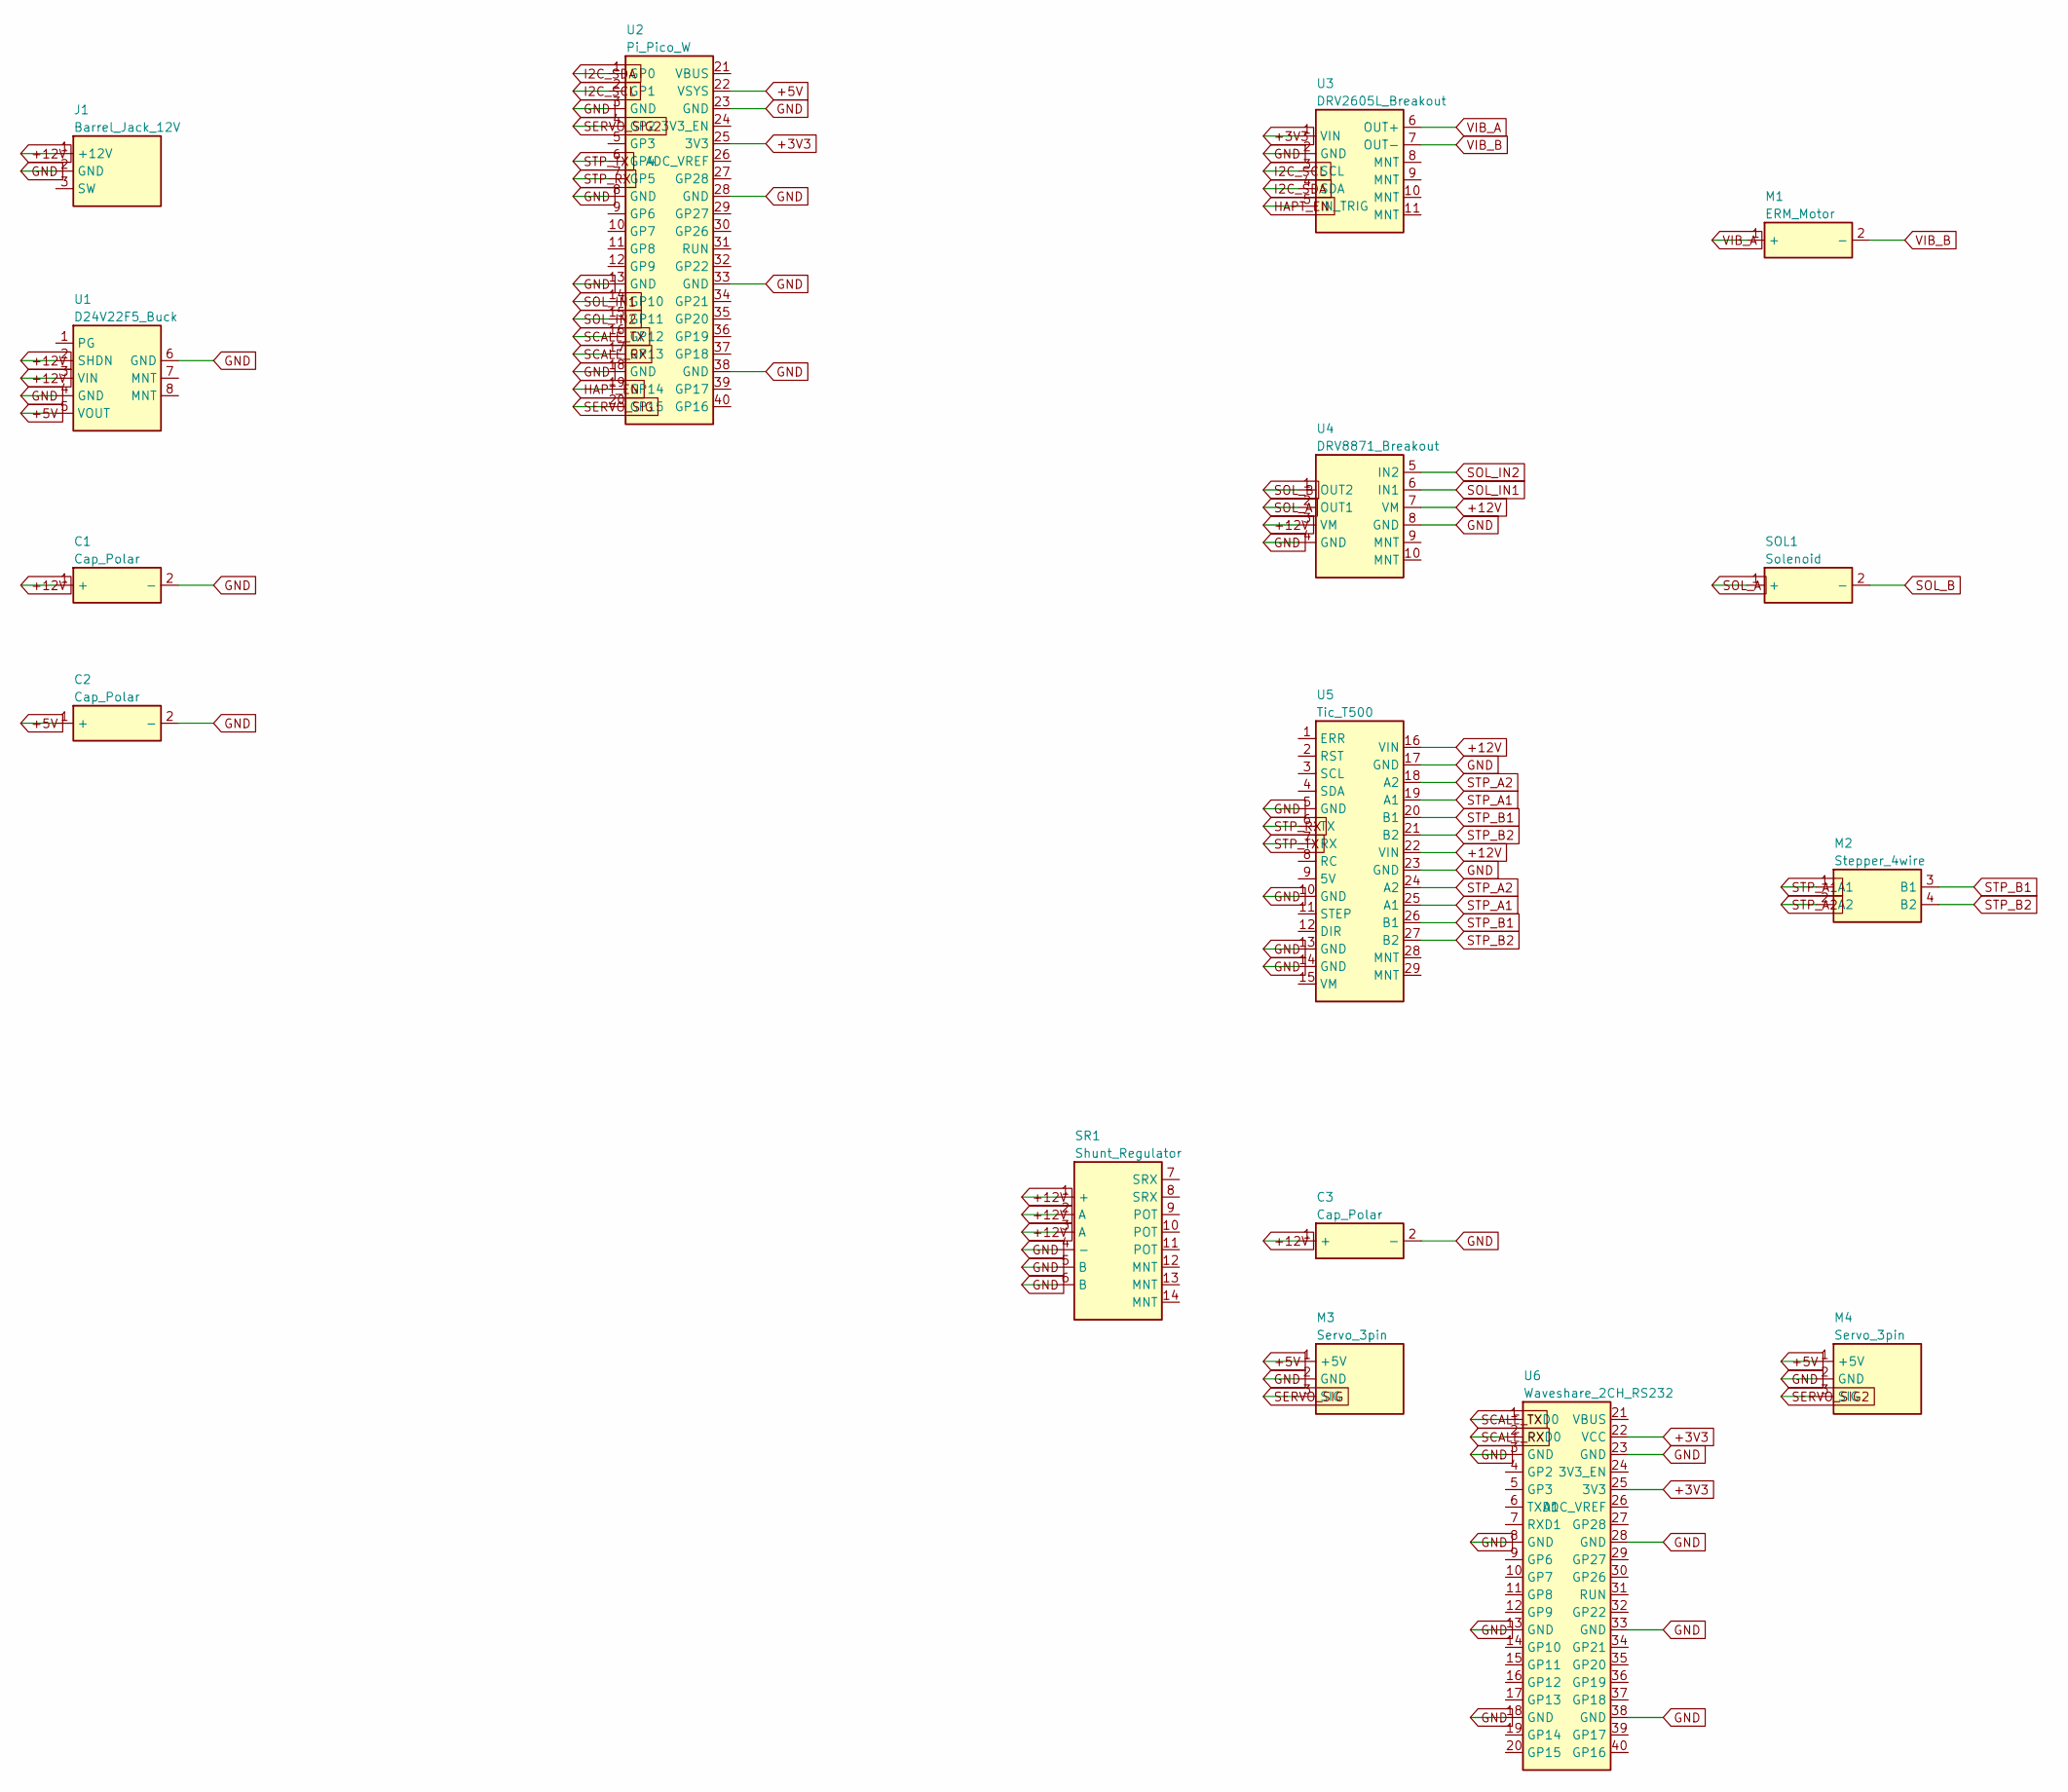
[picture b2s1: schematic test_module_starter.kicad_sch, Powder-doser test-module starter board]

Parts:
C1, C2, C3: Cap_Polar; CP_Radial_D8.0mm_P3.50mm
J1: Barrel_Jack_12V; BarrelJack_Horizontal
M1: ERM_Motor; PinHeader_1x02_P2.54mm_Vertical
M2: Stepper_4wire; PinHeader_1x04_P2.54mm_Vertical
M3, M4: Servo_3pin; PinHeader_1x03_P2.54mm_Vertical
SOL1: Solenoid; PinHeader_1x02_P2.54mm_Vertical
SR1: Shunt_Regulator
U1: D24V22F5_Buck
U2: Pi_Pico_W
U3: DRV2605L_Breakout
U4: DRV8871_Breakout
U5: Tic_T500
U6: Waveshare_2CH_RS232

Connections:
+3V3: U2.25 (3V3), U3.1 (VIN), U6.22 (VCC), U6.25 (3V3)
+5V: C2.1 (+), M3.1 (+5V), M4.1 (+5V), U1.5 (VOUT), U2.22 (VSYS)
+12V: C1.1 (+), C3.1 (+), J1.1 (+12V), SR1.1 (+), SR1.2 (A), SR1.3 (A), U1.2 (SHDN), U1.3 (VIN), U4.3 (VM), U4.7 (VM), U5.16 (VIN), U5.22 (VIN)
GND: C1.2 (-), C2.2 (-), C3.2 (-), J1.2 (GND), M3.2 (GND), M4.2 (GND), SR1.4 (-), SR1.5 (B), SR1.6 (B), U1.4 (GND), U1.6 (GND), U2.3 (GND), U2.8 (GND), U2.13 (GND), U2.18 (GND), U2.23 (GND), U2.28 (GND), U2.33 (GND), U2.38 (GND), U3.2 (GND), U4.4 (GND), U4.8 (GND), U5.5 (GND), U5.10 (GND), U5.13 (GND), U5.14 (GND), U5.17 (GND), U5.23 (GND), U6.3 (GND), U6.8 (GND), U6.13 (GND), U6.18 (GND), U6.23 (GND), U6.28 (GND), U6.33 (GND), U6.38 (GND)
HAPT_EN: U2.19 (GP14), U3.5 (IN_TRIG)
I2C_SCL: U2.2 (GP1), U3.3 (SCL)
I2C_SDA: U2.1 (GP0), U3.4 (SDA)
SCALE_RX: U2.17 (GP13), U6.2 (RXD0)
SCALE_TX: U2.16 (GP12), U6.1 (TXD0)
SERVO_SIG: M3.3 (SIG), U2.20 (GP15)
SERVO_SIG2: M4.3 (SIG), U2.4 (GP2)
SOL_A: SOL1.1 (+), U4.2 (OUT1)
SOL_B: SOL1.2 (-), U4.1 (OUT2)
SOL_IN1: U2.14 (GP10), U4.6 (IN1)
SOL_IN2: U2.15 (GP11), U4.5 (IN2)
STP_A1: M2.1 (A1), U5.19 (A1), U5.25 (A1)
STP_A2: M2.2 (A2), U5.18 (A2), U5.24 (A2)
STP_B1: M2.3 (B1), U5.20 (B1), U5.26 (B1)
STP_B2: M2.4 (B2), U5.21 (B2), U5.27 (B2)
STP_RX: U2.7 (GP5), U5.6 (TX)
STP_TX: U2.6 (GP4), U5.7 (RX)
VIB_A: M1.1 (+), U3.6 (OUT+)
VIB_B: M1.2 (-), U3.7 (OUT-)

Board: 2 copper layers, 16 parts (0 on the bottom side), 23 nets, no tracks yet.

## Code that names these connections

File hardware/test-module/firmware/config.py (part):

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# intentionally stay below GP16 and the rig is firmware-compatible with
# both Pico and Pico W.
# -----------------------------------------------------------------------
PIN_I2C_SDA   = 0          # DRV2605L SDA (I2C0)
PIN_I2C_SCL   = 1          # DRV2605L SCL (I2C0)

# Pololu Tic T500 stepper controller over UART1 (TTL serial).
PIN_TIC_TX    = 4          # Pico UART1 TX -> Tic RX
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TIC_BAUD      = 9600       # match the Tic's "Serial / I2C / USB" baud
TIC_READ_TIMEOUT_MS = 50   # how long to wait for a get-variable reply

PIN_SOL_IN1   = 10         # DRV8871 IN1
PIN_SOL_IN2   = 11         # DRV8871 IN2

# A&D HR-100A balance via a Waveshare Pico-2CH-RS232 module on UART0.
# The Waveshare board (SP3232EEN transceiver, the same RS-232 <-> 3.3 V
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# GP12/GP13 mux site instead.  The module's native channels (TXD0/RXD0 ->
# GP0/GP1, TXD1/RXD1 -> GP4/GP5) both collide with rig peripherals, so
# jumper the chosen channel out to GP12/GP13 (see hardware README step 8).
PIN_SCALE_TX  = 12         # Pico UART0 TX -> module TXD -> scale RXD
PIN_SCALE_RX  = 13         # Pico UART0 RX <- module RXD <- scale TXD
SCALE_UART_ID = 0          # RP2040 UART0 (TX=GP12, RX=GP13)

PIN_HAPT_EN   = 14         # DRV2605L EN / IN_TRIG (tie high to enable)
PIN_SERVO_SIG  = 15        # Servo 1 PWM signal (dispensing-angle axis)
PIN_SERVO_SIG2 = 2         # Servo 2 PWM signal (opposite side of baseplate)


# -----------------------------------------------------------------------
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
